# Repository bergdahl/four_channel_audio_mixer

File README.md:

# four_channel_audio_mixer

Work in progress....

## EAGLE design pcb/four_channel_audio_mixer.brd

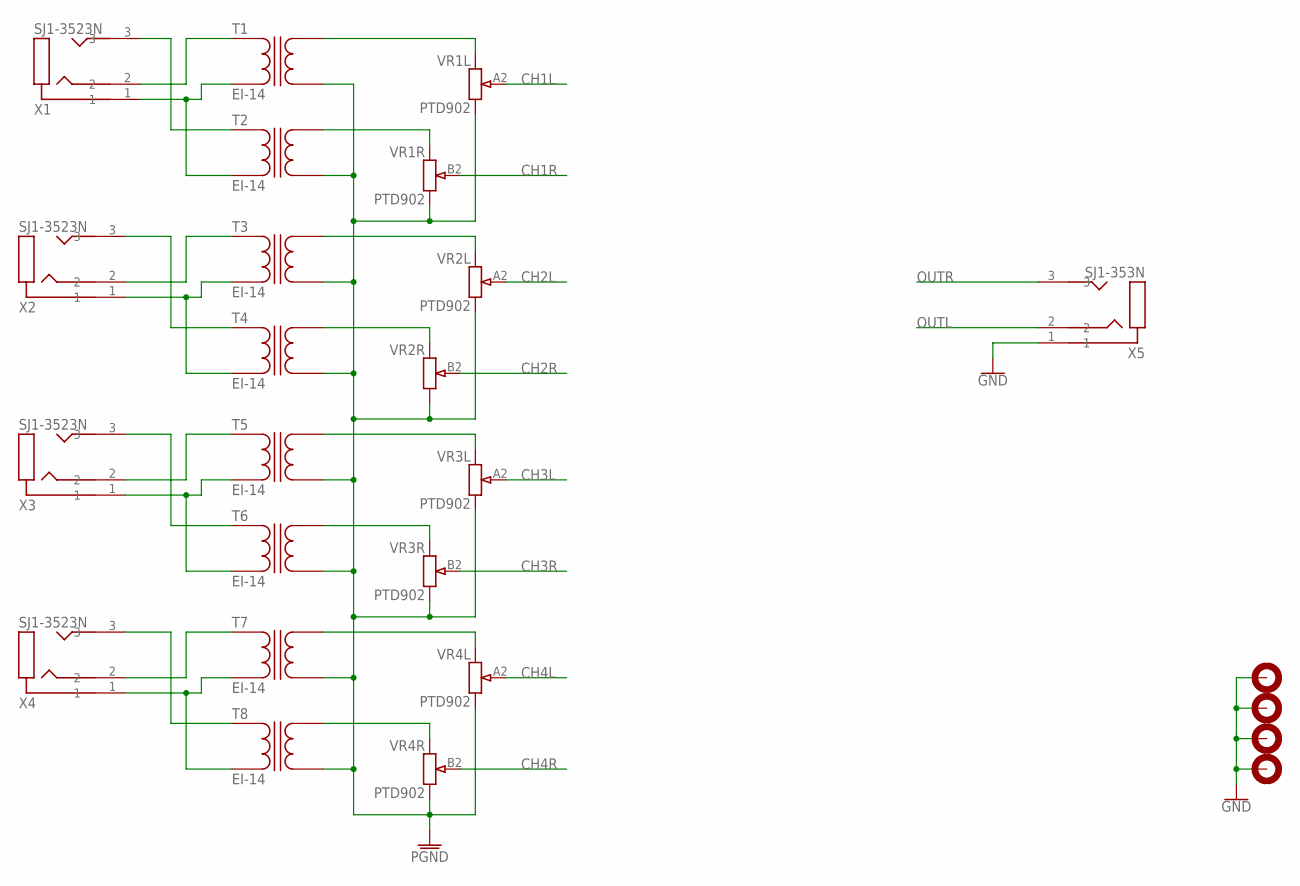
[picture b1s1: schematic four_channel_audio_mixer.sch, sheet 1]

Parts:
H1, H2, H3, H4: MOUNTHOLE-PAD3.2; 3.2-PAD
T1, T2, T3, T4, T5, T6, T7, T8: EI-14; TRANSFORMER_EI14
VR1, VR2, VR3, VR4: PTD902; POT-PTD902
X1, X2, X3, X4: SJ1-3523N; AUDIO-3.5-SJ1-3523N
X5: SJ1-353N; AUDIO-3.5-SJ1-3523N

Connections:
CH1L: VR1.A2 (2); also elsewhere on the board
CH1R: VR1.B2 (2); also elsewhere on the board
CH2L: VR2.A2 (2); also elsewhere on the board
CH2R: VR2.B2 (2); also elsewhere on the board
CH3L: VR3.A2 (2); also elsewhere on the board
CH3R: VR3.B2 (2); also elsewhere on the board
CH4L: VR4.A2 (2); also elsewhere on the board
CH4R: VR4.B2 (2); also elsewhere on the board
GND: H1.B3,2, H2.B3,2, H3.B3,2, H4.B3,2, X5.1; also elsewhere on the board
unnamed: T1.A1, X1.2
unnamed: T2.A1, X1.3
unnamed: T3.A2, T4.A2, X2.1
unnamed: T1.A2, T2.A2, X1.1
unnamed: T1.B2, VR1.A3 (3)
unnamed: T2.B2, VR1.B3 (3)
unnamed: T3.A1, X2.2
unnamed: T4.A1, X2.3
unnamed: T5.A2, T6.A2, X3.1
unnamed: T5.A1, X3.2
unnamed: T6.A1, X3.3
unnamed: T7.A2, T8.A2, X4.1
unnamed: T7.A1, X4.2
unnamed: T8.A1, X4.3
unnamed: T3.B2, VR2.A3 (3)
unnamed: T4.B2, VR2.B3 (3)
unnamed: T5.B2, VR3.A3 (3)
unnamed: T6.B2, VR3.B3 (3)
unnamed: T7.B2, VR4.A3 (3)
unnamed: T8.B2, VR4.B3 (3)
OUTL: X5.2; also elsewhere on the board
OUTR: X5.3; also elsewhere on the board
PGND: T1.B1, T2.B1, T3.B1, T4.B1, T5.B1, T6.B1, T7.B1, T8.B1, VR1.A1 (1), VR1.B1 (1), VR2.A1 (1), VR2.B1 (1), VR3.A1 (1), VR3.B1 (1), VR4.A1 (1), VR4.B1 (1); also elsewhere on the board

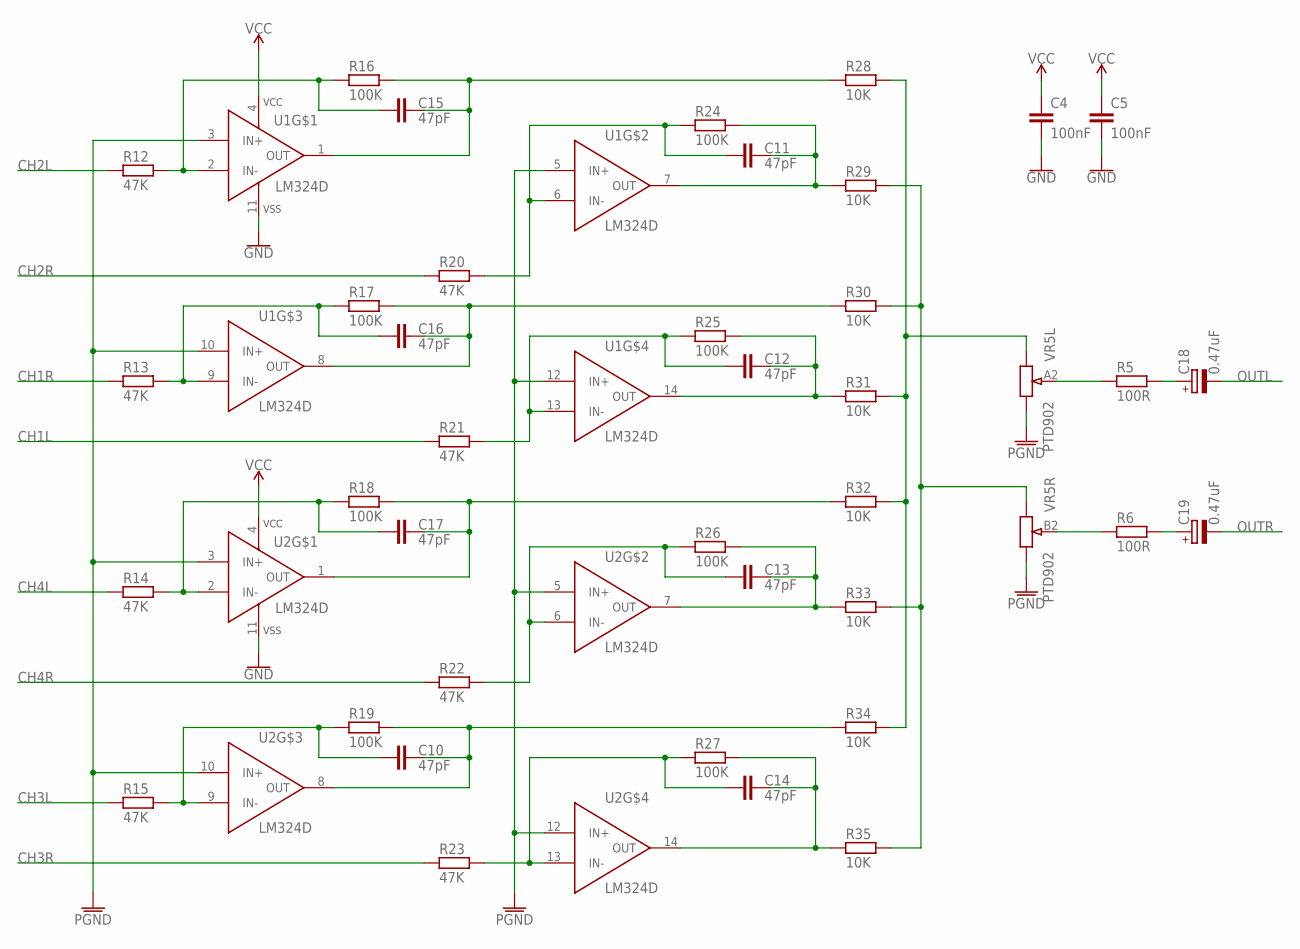
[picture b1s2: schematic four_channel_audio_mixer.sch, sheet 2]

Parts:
C4, C5: 100nF; C0603
C10, C11, C12, C13, C14, C15, C16, C17: 47pF; C0603
C18, C19: 0.47uF; WE-4.0X5.5
R5, R6: 100R; R0603
R12, R13, R14, R15, R20, R21, R22, R23: 47K; R0603
R16, R17, R18, R19, R24, R25, R26, R27: 100K; R0603
R28, R29, R30, R31, R32, R33, R34, R35: 10K; R0603
U1, U2: LM324D; SOIC-14
VR5: PTD902; POT-PTD902

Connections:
CH1L: R21.1; also elsewhere on the board
CH1R: R13.1; also elsewhere on the board
CH2L: R12.1; also elsewhere on the board
CH2R: R20.1; also elsewhere on the board
CH3L: R15.1; also elsewhere on the board
CH3R: R23.1; also elsewhere on the board
CH4L: R14.1; also elsewhere on the board
CH4R: R22.1; also elsewhere on the board
F1L: C12.2, R21.2, R25.1, U1.13 (IN-)
F1R: C16.2, R13.2, R17.1, U1.9 (IN-)
F2L: C11.2, R20.2, R24.1, U1.6 (IN-)
F2R: C15.2, R12.2, R16.1, U1.2 (IN-)
GND: C4.2, C5.2, U1.11 (VSS), U2.11 (VSS); also elsewhere on the board
MIXL: R28.2, R31.2, R32.2, R34.2, VR5.A3 (3)
MIXR: R29.2, R30.2, R33.2, R35.2, VR5.B3 (3)
unnamed: C18.+, R5.2
unnamed: R5.1, VR5.A2 (2)
unnamed: C19.+, R6.2
unnamed: R6.1, VR5.B2 (2)
unnamed: C15.1, R16.2, R28.1, U1.1 (OUT)
unnamed: C11.1, R24.2, R29.1, U1.7 (OUT)
unnamed: C16.1, R17.2, R30.1, U1.8 (OUT)
unnamed: C12.1, R25.2, R31.1, U1.14 (OUT)
unnamed: C17.1, R18.2, R32.1, U2.1 (OUT)
unnamed: C17.2, R14.2, R18.1, U2.2 (IN-)
unnamed: C13.1, R26.2, R33.1, U2.7 (OUT)
unnamed: C10.1, R19.2, R34.1, U2.8 (OUT)
unnamed: C10.2, R15.2, R19.1, U2.9 (IN-)
unnamed: C14.1, R27.2, R35.1, U2.14 (OUT)
unnamed: C13.2, R22.2, R26.1, U2.6 (IN-)
unnamed: C14.2, R23.2, R27.1, U2.13 (IN-)
OUTL: C18.-; also elsewhere on the board
OUTR: C19.-; also elsewhere on the board
PGND: U1.3 (IN+), U1.5 (IN+), U1.10 (IN+), U1.12 (IN+), U2.3 (IN+), U2.5 (IN+), U2.10 (IN+), U2.12 (IN+), VR5.A1 (1), VR5.B1 (1); also elsewhere on the board
VCC: C4.1, C5.1, U1.4 (VCC), U2.4 (VCC); also elsewhere on the board

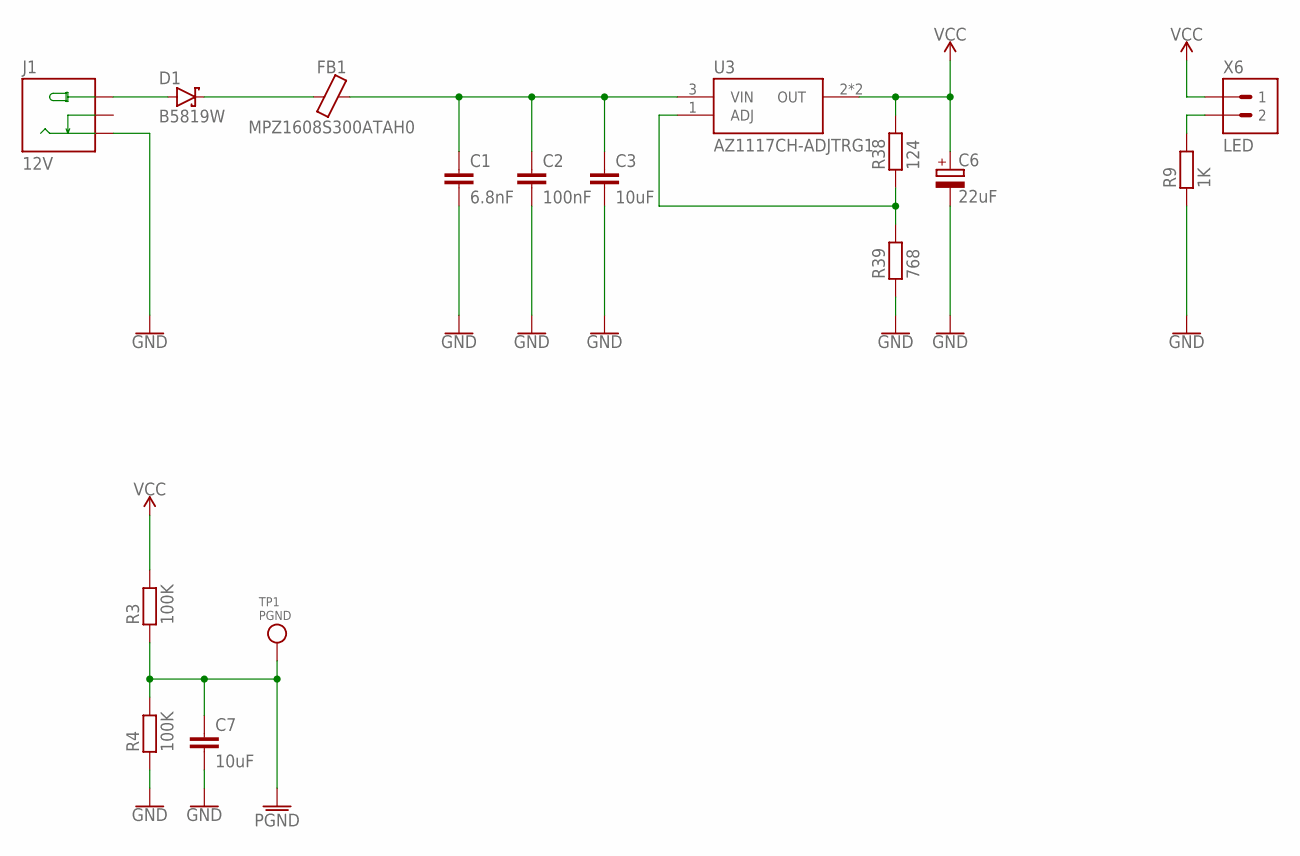
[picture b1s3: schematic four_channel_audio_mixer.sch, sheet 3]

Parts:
C1: 6.8nF; C0603
C2: 100nF; C0603
C3, C7: 10uF; C0603
C6: 22uF; CASE-B-3528
D1: B5819W; SOD-123
FB1: MPZ1608S300ATAH0; MPZ1608
J1: 12V; 5DJ20DC02-03T0BLB-01-14.5X10.7.0X9.0MM
R3, R4: 100K; R0603
R9: 1K; R0603
R38: 124; R0603
R39: 768; R0603
TP1: PGND; 1X01_ROUND
U3: AZ1117CH-ADJTRG1; SOT-223
X6: LED; 1X02P-2.54

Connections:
GND: C1.2, C2.2, C3.2, C6.-, C7.2, J1.-1 (-), R4.1, R9.1, R39.1; also elsewhere on the board
unnamed: R9.2, X6.2
unnamed: D1.A, J1.+
unnamed: R38.1, R39.2, U3.1 (ADJ)
unnamed: C1.1, C2.1, C3.1, FB1.2, U3.3 (VIN)
unnamed: D1.C, FB1.1
PGND: C7.1, R3.1, R4.2, TP1.1; also elsewhere on the board
VCC: C6.+, R3.2, R38.2, U3.2 (OUT), U3.4 (OUT), X6.1; also elsewhere on the board

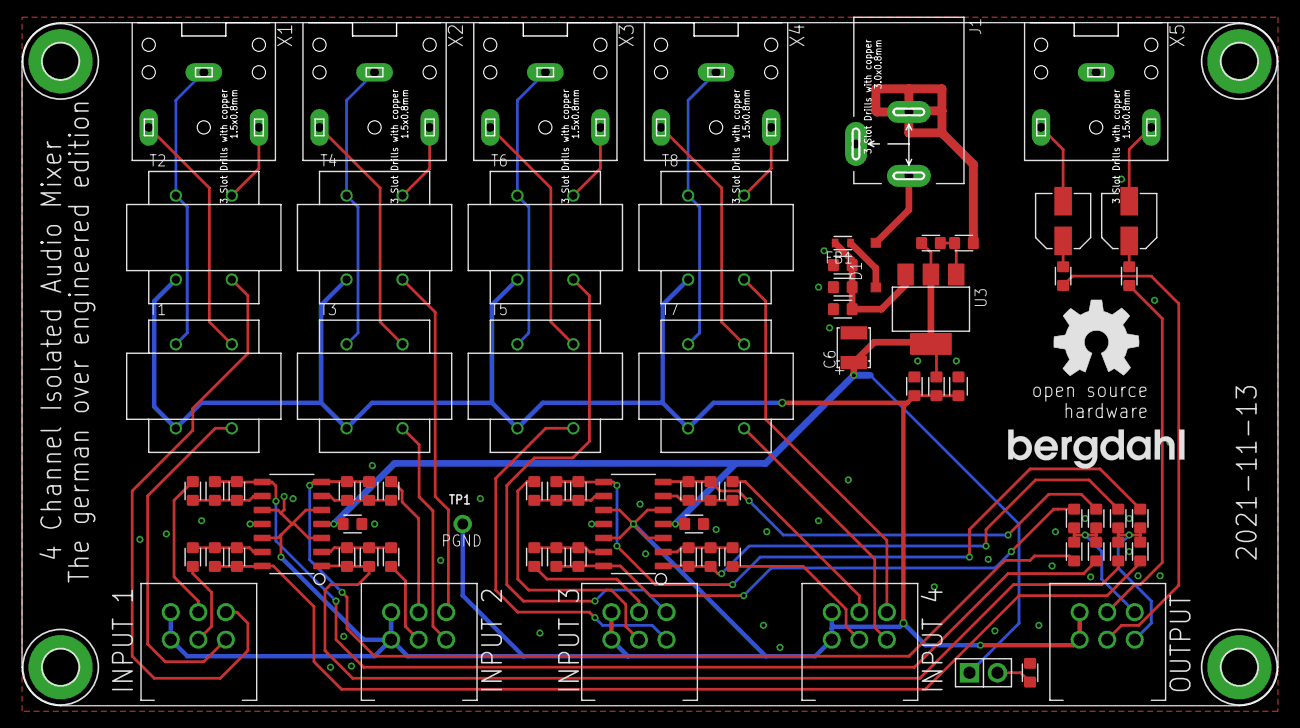
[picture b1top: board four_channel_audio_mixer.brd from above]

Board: 2 copper layers, 113.8 x 61.9 mm, 80 parts (0 on the bottom side), 60 nets.

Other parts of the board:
U$1: BERGDAHL-20MM-TPLACE
U$2: OSHW-8MM-TPLACE

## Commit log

2021-11-13 Version 2021-11-13
